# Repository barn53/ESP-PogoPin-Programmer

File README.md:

# ESP Programmer with PogoPins
- Used to program ESP-01, ESP-12E/F modules

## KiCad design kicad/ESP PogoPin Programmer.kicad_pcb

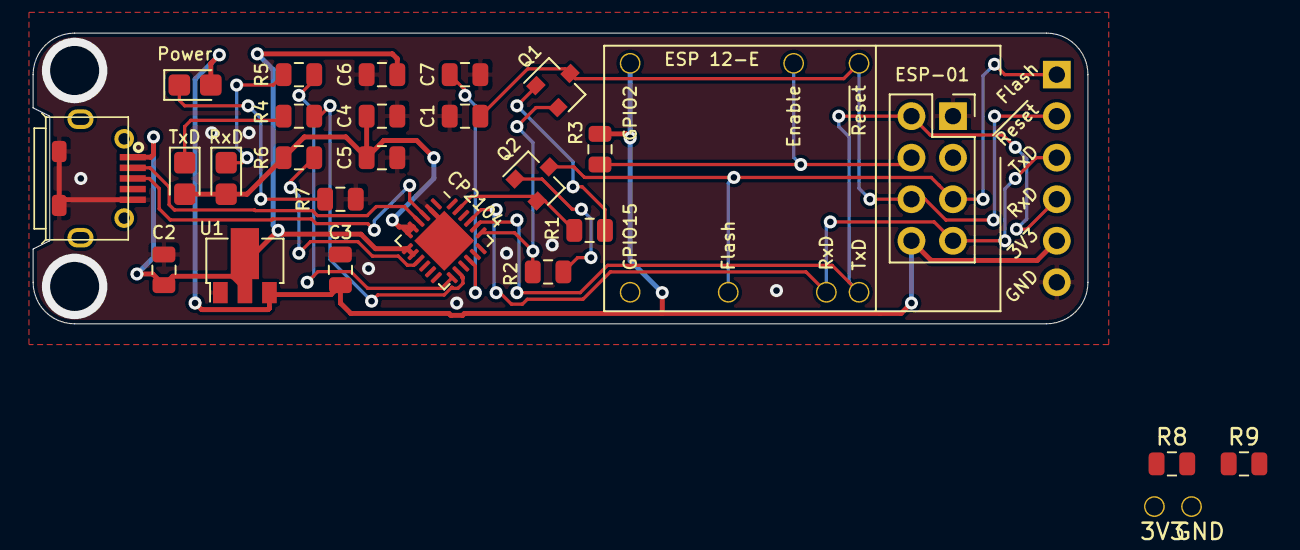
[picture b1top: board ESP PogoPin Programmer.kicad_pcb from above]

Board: 2 copper layers, 64.5 x 17.8 mm, 36 parts (1 on the bottom side), 24 nets.

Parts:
C1, C4: 100n; C_0805_2012Metric
C2, C6: 1u; C_0805_2012Metric
C3, C5, C7: 4u7; C_0805_2012Metric
D1: TxD; LED_0805_2012Metric_Castellated
D2: RxD; LED_0805_2012Metric_Castellated
D3: Power; LED_0805_2012Metric_Castellated
J1: USB_B_Micro; MicroUSB_through_hole_fixing
J2: ~Reset; PogoPin_vertical
J3: TxD; PogoPin_vertical
J4: RxD; PogoPin_vertical
J5: Enable; PogoPin_vertical
J6: Flash; PogoPin_vertical
J7: GPIO2; PogoPin_vertical
J8: GPIO15; PogoPin_vertical
J9: ESP-01; PinSocket_2x04_P2.54mm_Vertical
J10: Conn_01x06; PinHeader_1x06_P2.54mm_Vertical
J11: 3V3; PogoPin_vertical
J12: GND; PogoPin_vertical
Q1, Q2: S8050_J3Y; SOT-23
QR*****: https://barn53.de/esp-programmer; __barn53.de_esp-programmer
R1, R2, R3, R8, R9: 10k; R_0805_2012Metric
R4, R5, R7: 180; R_0805_2012Metric
R6: 4k7; R_0805_2012Metric
U1: BL8565; SOT-89-3
U2: CP2104; QFN-24-1EP_4x4mm_P0.5mm_EP2.6x2.6mm

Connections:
/3V3: C3.1, D3.2, J9.8, J10.5, J11.1, R3.2, R8.2, U1.3
/D+: J1.3, U2.3
/D-: J1.2, U2.4
/DTR: Q2.2, R1.2, U2.23
/Enable: J5.1, J9.4, R3.1
/Flash: J6.1, J9.5, J10.1, Q2.3
/GPIO2: J7.1, J9.3, R8.1
/GPIO15: J8.1, R9.2
/GPIO.0: R4.2, U2.14
/GPIO.1: R5.2, U2.13
/RTS: Q1.2, R2.2, U2.19
/RxD: J3.1, J9.2, J10.4, U2.20
/TxD: J4.1, J9.7, J10.3, U2.21
/VBus: C2.1, C6.1, J1.1, U1.2, U2.7, U2.8
/VDD: C4.1, C5.1, D1.2, D2.2, R6.1, U2.5, U2.6
/~Reset: C1.1, J2.1, J9.6, J10.2, Q1.3
GND: C1.2, C2.2, C3.2, C4.2, C5.2, C6.2, C7.2, J1.5, J1.6, J9.1, J10.6, J12.1, R7.1, R9.1, U1.1, U2.2, U2.25
unnamed: C7.1, U2.16
unnamed: D1.1, R4.1
unnamed: D2.1, R5.1
unnamed: D3.1, R7.2
unnamed: Q1.1, R1.1
unnamed: Q2.1, R2.1
unnamed: R6.2, U2.9

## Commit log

2020-01-15 project setup
2020-02-04 saving commit
2020-10-07 Stuff for first revision
2021-01-19 minor
